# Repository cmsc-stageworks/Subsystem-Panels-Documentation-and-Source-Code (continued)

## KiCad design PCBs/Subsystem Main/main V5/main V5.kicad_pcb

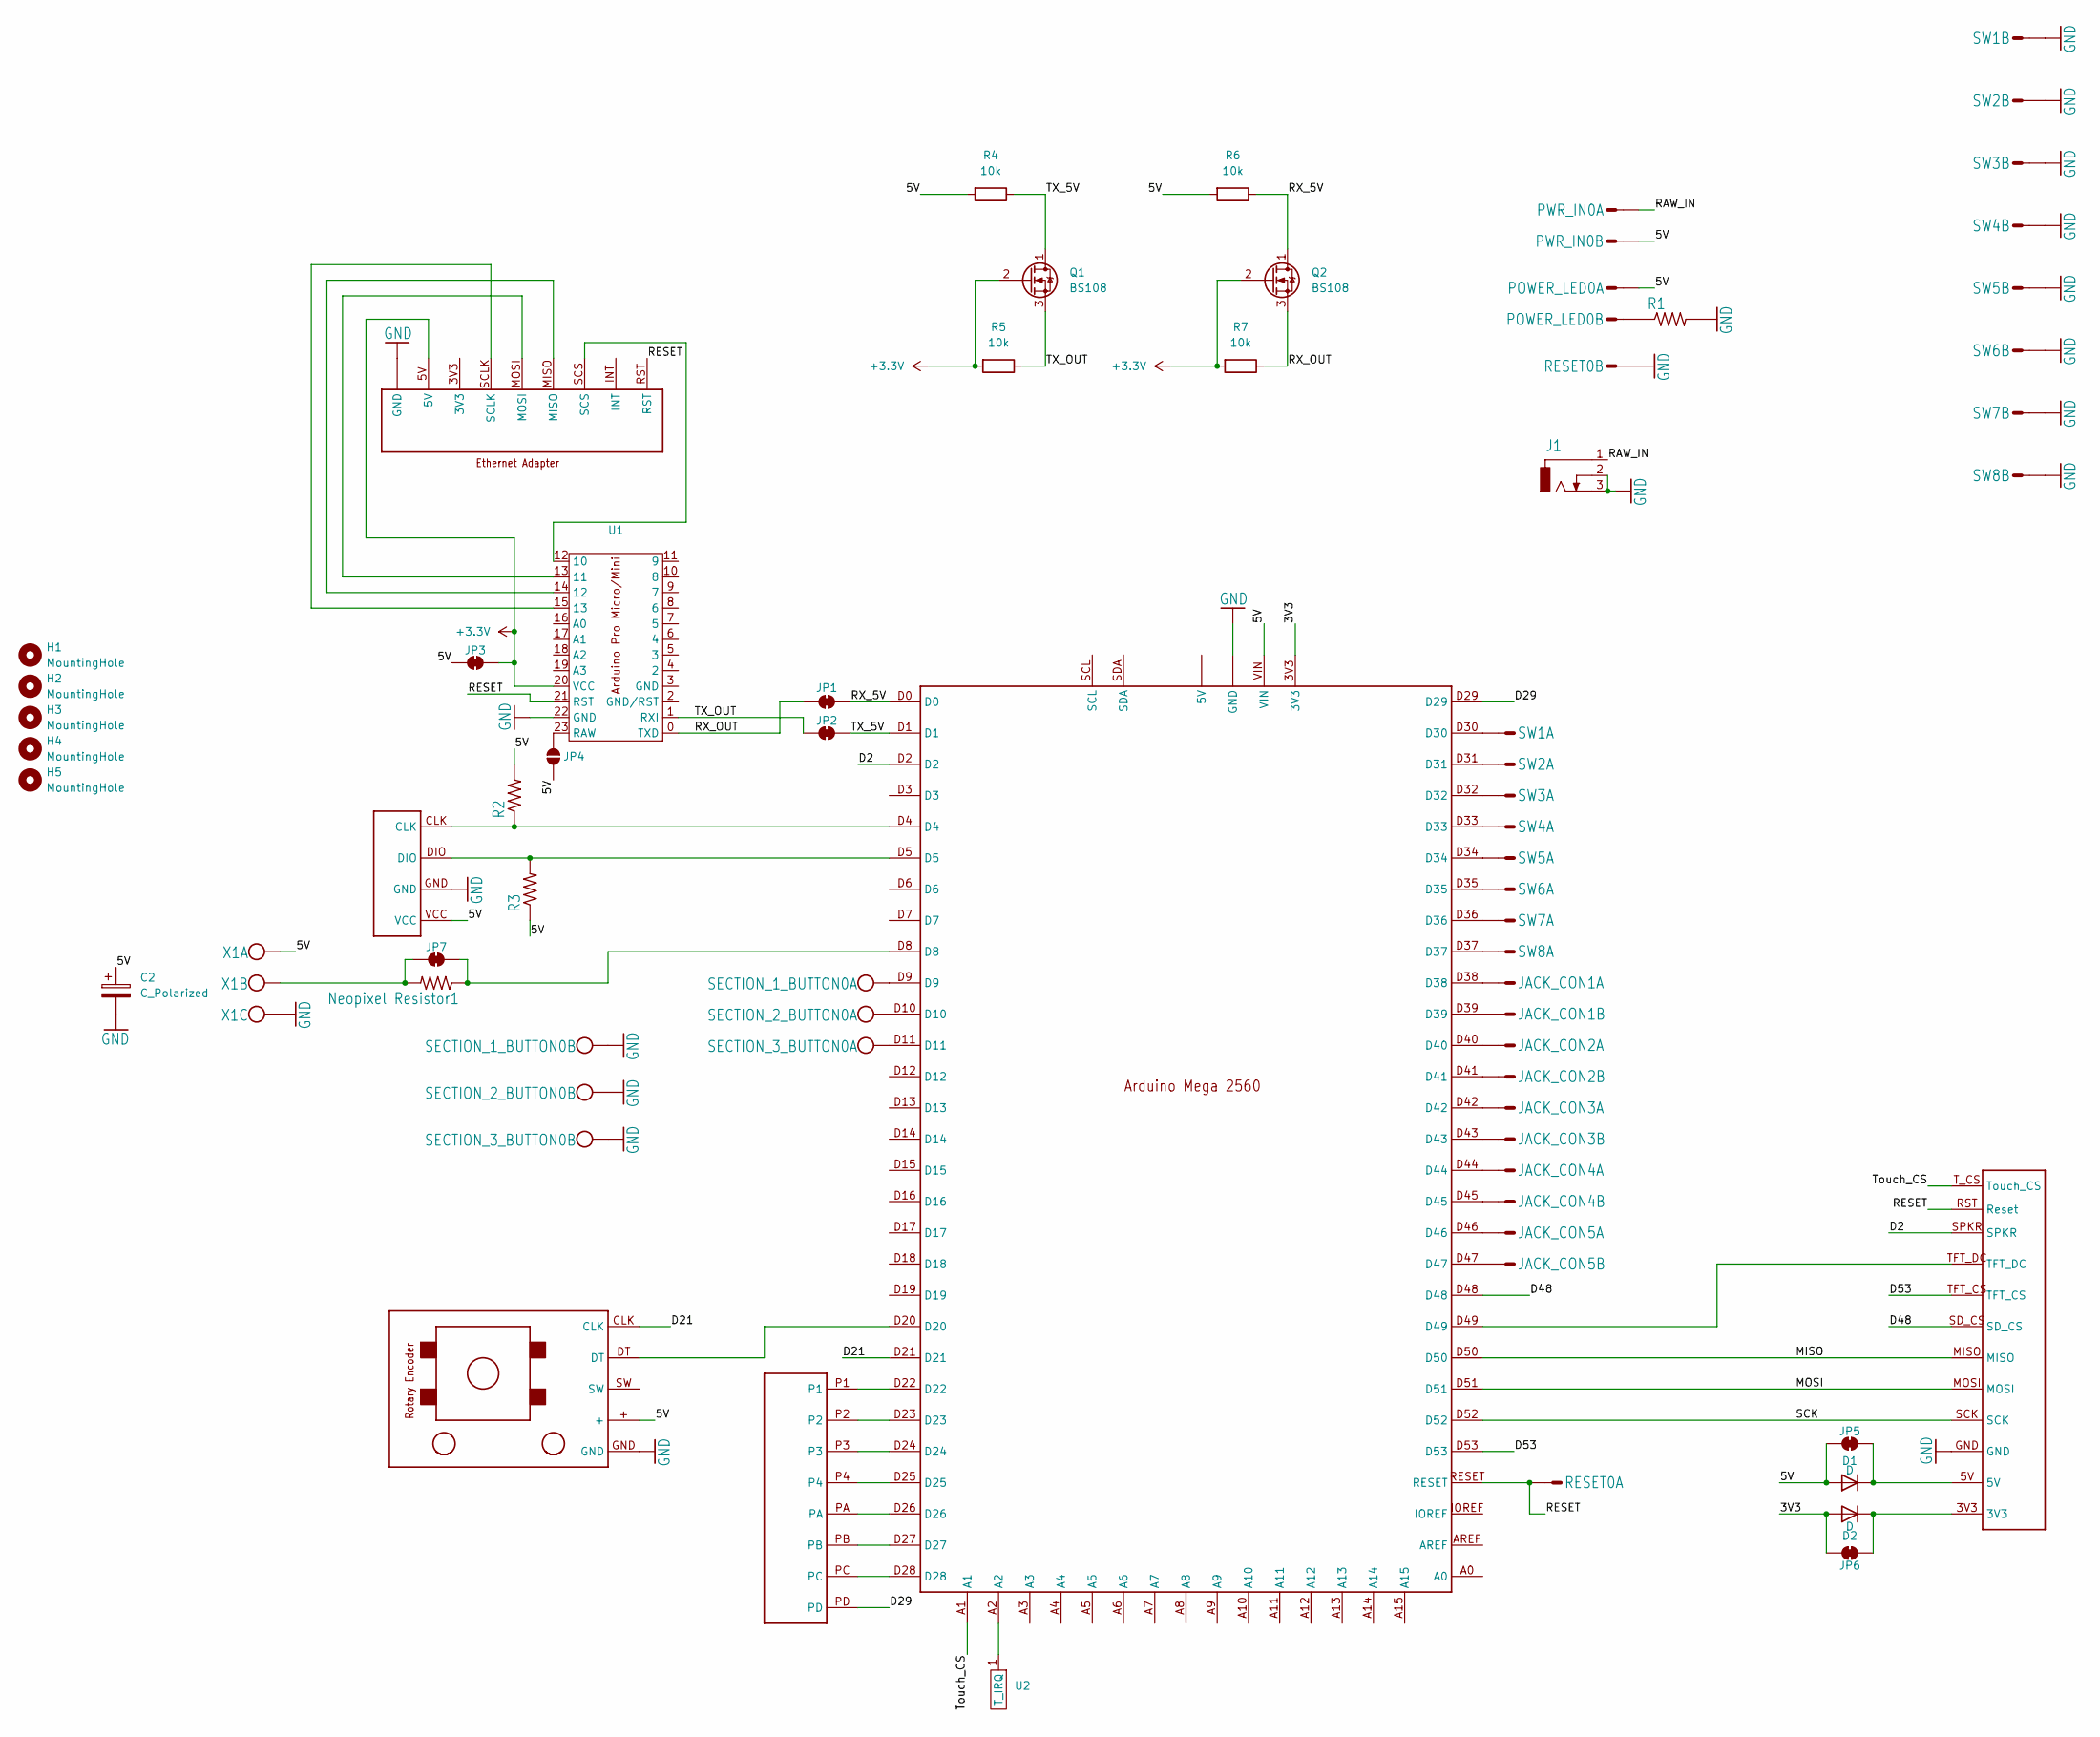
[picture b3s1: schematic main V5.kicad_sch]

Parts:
11: ETHERNET_ADAPTER
C1: SPI_HEADER_RIBBON_CONNECTOR_V2
C2: C_Polarized; CP_Radial_D10.0mm_P2.50mm_P5.00mm
D1, D2: D; D_DO-15_P10.16mm_Horizontal
H1, H2, H3, H4, H5: MountingHole; MountingHole_3.2mm_M3
J1: DCJ0303; BarrelJack_Horizontal
JACK_CON1, JACK_CON2, JACK_CON3, JACK_CON4, JACK_CON5: L02P; JST_EH_B2B-EH-A_1x02_P2.50mm_Vertical
JP1, JP2, JP3, JP5, JP6, JP7: SolderJumper_2_Bridged; SolderJumper-2_P1.3mm_Bridged_RoundedPad1.0x1.5mm
JP4: SolderJumper_2_Open; SolderJumper-2_P1.3mm_Open_TrianglePad1.0x1.5mm
Neopixel Resistor1: 350 ohm; R_Axial_DIN0204_L3.6mm_D1.6mm_P7.62mm_Horizontal
POWER_LED0: L02P; JST_EH_B2B-EH-A_1x02_P2.50mm_Vertical
PWR_IN0: L02P; JST_EH_B2B-EH-A_1x02_P2.50mm_Vertical
Q1, Q2: BS108; TO-92_Inline
R1: 220 ohm; R_Axial_DIN0204_L3.6mm_D1.6mm_P7.62mm_Horizontal
R2: 10K; R_Axial_DIN0204_L3.6mm_D1.6mm_P7.62mm_Horizontal
R3, R4, R5, R6, R7: 10k; R_Axial_DIN0204_L3.6mm_D1.6mm_P7.62mm_Horizontal
RESET0: L02P; JST_EH_B2B-EH-A_1x02_P2.50mm_Vertical
SECTION_1_BUTTON0, SECTION_2_BUTTON0, SECTION_3_BUTTON0: W237-102; JST_EH_B2B-EH-A_1x02_P2.50mm_Vertical
SW1, SW2, SW3, SW4, SW5, SW6, SW7, SW8: L02P; JST_EH_B2B-EH-A_1x02_P2.50mm_Vertical
U1: Arduino Pro Micro (Mini)
U2: T_IRQ
U$1: ARDUINO_MEGAMIRROR; ARDUINO_MEGA_MIRROR
U$2: 7_SEG_DISPLAY
U$4: BUTTON_GRID_HEADER; BUTTON_GRID_HEADER_RIBBON_CONNECTOR
U$5: ROTARY_ENCODER
X1: W237-103; TerminalBlock_bornier-3_P5.08mm

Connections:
+3.3V: 11.5V, JP3.2 (B), Q1.2 (G), Q2.2 (G), R5.2, R7.2, U1.20 (VCC)
/3V3: D2.2 (A), JP6.2 (B), U$1.3V3
/5V: C2.1, D1.2 (A), JP3.1 (A), JP4.1 (A), JP5.1 (A), POWER_LED0.1 (S), PWR_IN0.2 (S), R2.2, R3.1, R4.2, R6.2, U$1.VIN, U$2.VCC, U$5.+, X1.1 (KL)
/D2: C1.SPKR, U$1.D2
/D21: U$1.D21, U$5.CLK
/D29: U$1.D29, U$4.PD
/D48: C1.SD_CS, U$1.D48
/D53: C1.TFT_CS, U$1.D53
/MISO: C1.MISO, U$1.D50
/MOSI: C1.MOSI, U$1.D51
/RAW_IN: J1.1, PWR_IN0.1 (S)
/RESET: 11.RST, C1.RST (Reset), RESET0.1 (S), U1.21 (RST), U$1.RESET
/RX_5V: JP1.2 (B), Q2.1 (D), R6.1, U$1.D0
/RX_OUT: JP1.1 (A), Q2.3 (S), R7.1, U1.0 (TXD)
/SCK: C1.SCK, U$1.D52
/TX_5V: JP2.2 (B), Q1.1 (D), R4.1, U$1.D1
/TX_OUT: JP2.1 (A), Q1.3 (S), R5.1, U1.1 (RXI)
/Touch_CS: C1.T_CS (Touch_CS), U$1.A1
GND: 11.GND@1 (GND), 11.GND@2 (GND), C1.GND, C2.2, J1.2, J1.3, R1.2, RESET0.2 (S), SECTION_1_BUTTON0.2 (KL), SECTION_2_BUTTON0.2 (KL), SECTION_3_BUTTON0.2 (KL), SW1.2 (S), SW2.2 (S), SW3.2 (S), SW4.2 (S), SW5.2 (S), SW6.2 (S), SW7.2 (S), SW8.2 (S), U1.22 (GND), U$1.GND@1 (GND), U$1.GND@2 (GND), U$1.GND@3 (GND), U$1.GND@4 (GND), U$1.GND@5 (GND), U$2.GND, U$5.GND, X1.3 (KL)
unnamed: C1.TFT_DC, U$1.D49
unnamed: C1.5V, D1.1 (K), JP5.2 (B)
unnamed: C1.3V3, D2.1 (K), JP6.1 (A)
unnamed: JACK_CON1.1 (S), U$1.D38
unnamed: JACK_CON1.2 (S), U$1.D39
unnamed: JACK_CON2.1 (S), U$1.D40
unnamed: JACK_CON2.2 (S), U$1.D41
unnamed: JACK_CON3.1 (S), U$1.D42
unnamed: JACK_CON3.2 (S), U$1.D43
unnamed: JACK_CON4.1 (S), U$1.D44
unnamed: JACK_CON4.2 (S), U$1.D45
unnamed: JACK_CON5.1 (S), U$1.D46
unnamed: JACK_CON5.2 (S), U$1.D47
unnamed: JP4.2 (B), U1.23 (RAW)
unnamed: JP7.1 (A), Neopixel Resistor1.2, X1.2 (KL)
unnamed: JP7.2 (B), Neopixel Resistor1.1, U$1.D8
unnamed: POWER_LED0.2 (S), R1.1
unnamed: R2.1, U$1.D4, U$2.CLK
unnamed: R3.2, U$1.D5, U$2.DIO
unnamed: SECTION_1_BUTTON0.1 (KL), U$1.D9
unnamed: SECTION_2_BUTTON0.1 (KL), U$1.D10
unnamed: SECTION_3_BUTTON0.1 (KL), U$1.D11
unnamed: SW1.1 (S), U$1.D30
unnamed: SW2.1 (S), U$1.D31
unnamed: SW3.1 (S), U$1.D32
unnamed: SW4.1 (S), U$1.D33
unnamed: SW5.1 (S), U$1.D34
unnamed: SW6.1 (S), U$1.D35
unnamed: SW7.1 (S), U$1.D36
unnamed: SW8.1 (S), U$1.D37
unnamed: 11.SCS, U1.12 (10)
unnamed: 11.MOSI, U1.13 (11)
unnamed: 11.MISO, U1.14 (12)
unnamed: 11.SCLK, U1.15 (13)
unnamed: U2.1 (T_IRQ), U$1.A2
unnamed: U$1.5V@1 (5V), U$1.5V@2 (5V), U$1.5V@3 (5V)
unnamed: U$1.D20, U$5.DT
unnamed: U$1.D22, U$4.P1
unnamed: U$1.D23, U$4.P2
unnamed: U$1.D24, U$4.P3
unnamed: U$1.D25, U$4.P4
unnamed: U$1.D26, U$4.PA
unnamed: U$1.D27, U$4.PB
unnamed: U$1.D28, U$4.PC

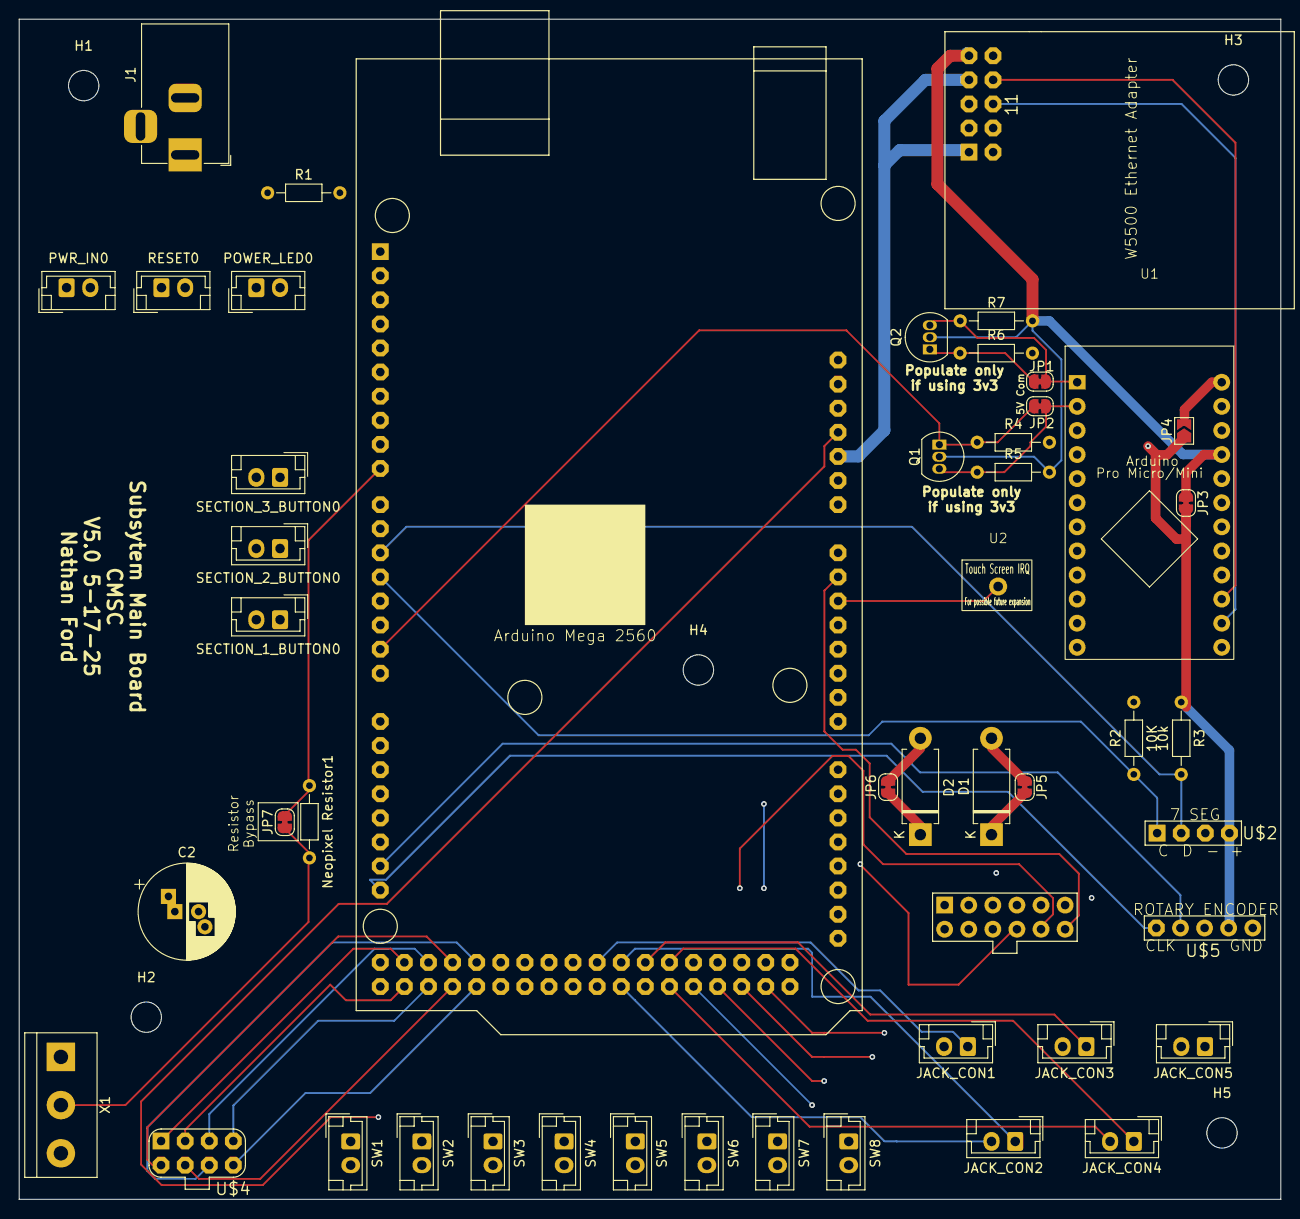
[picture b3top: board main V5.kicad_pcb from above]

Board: 4 copper layers, 133.0 x 124.4 mm, 54 parts (0 on the bottom side), 63 nets.

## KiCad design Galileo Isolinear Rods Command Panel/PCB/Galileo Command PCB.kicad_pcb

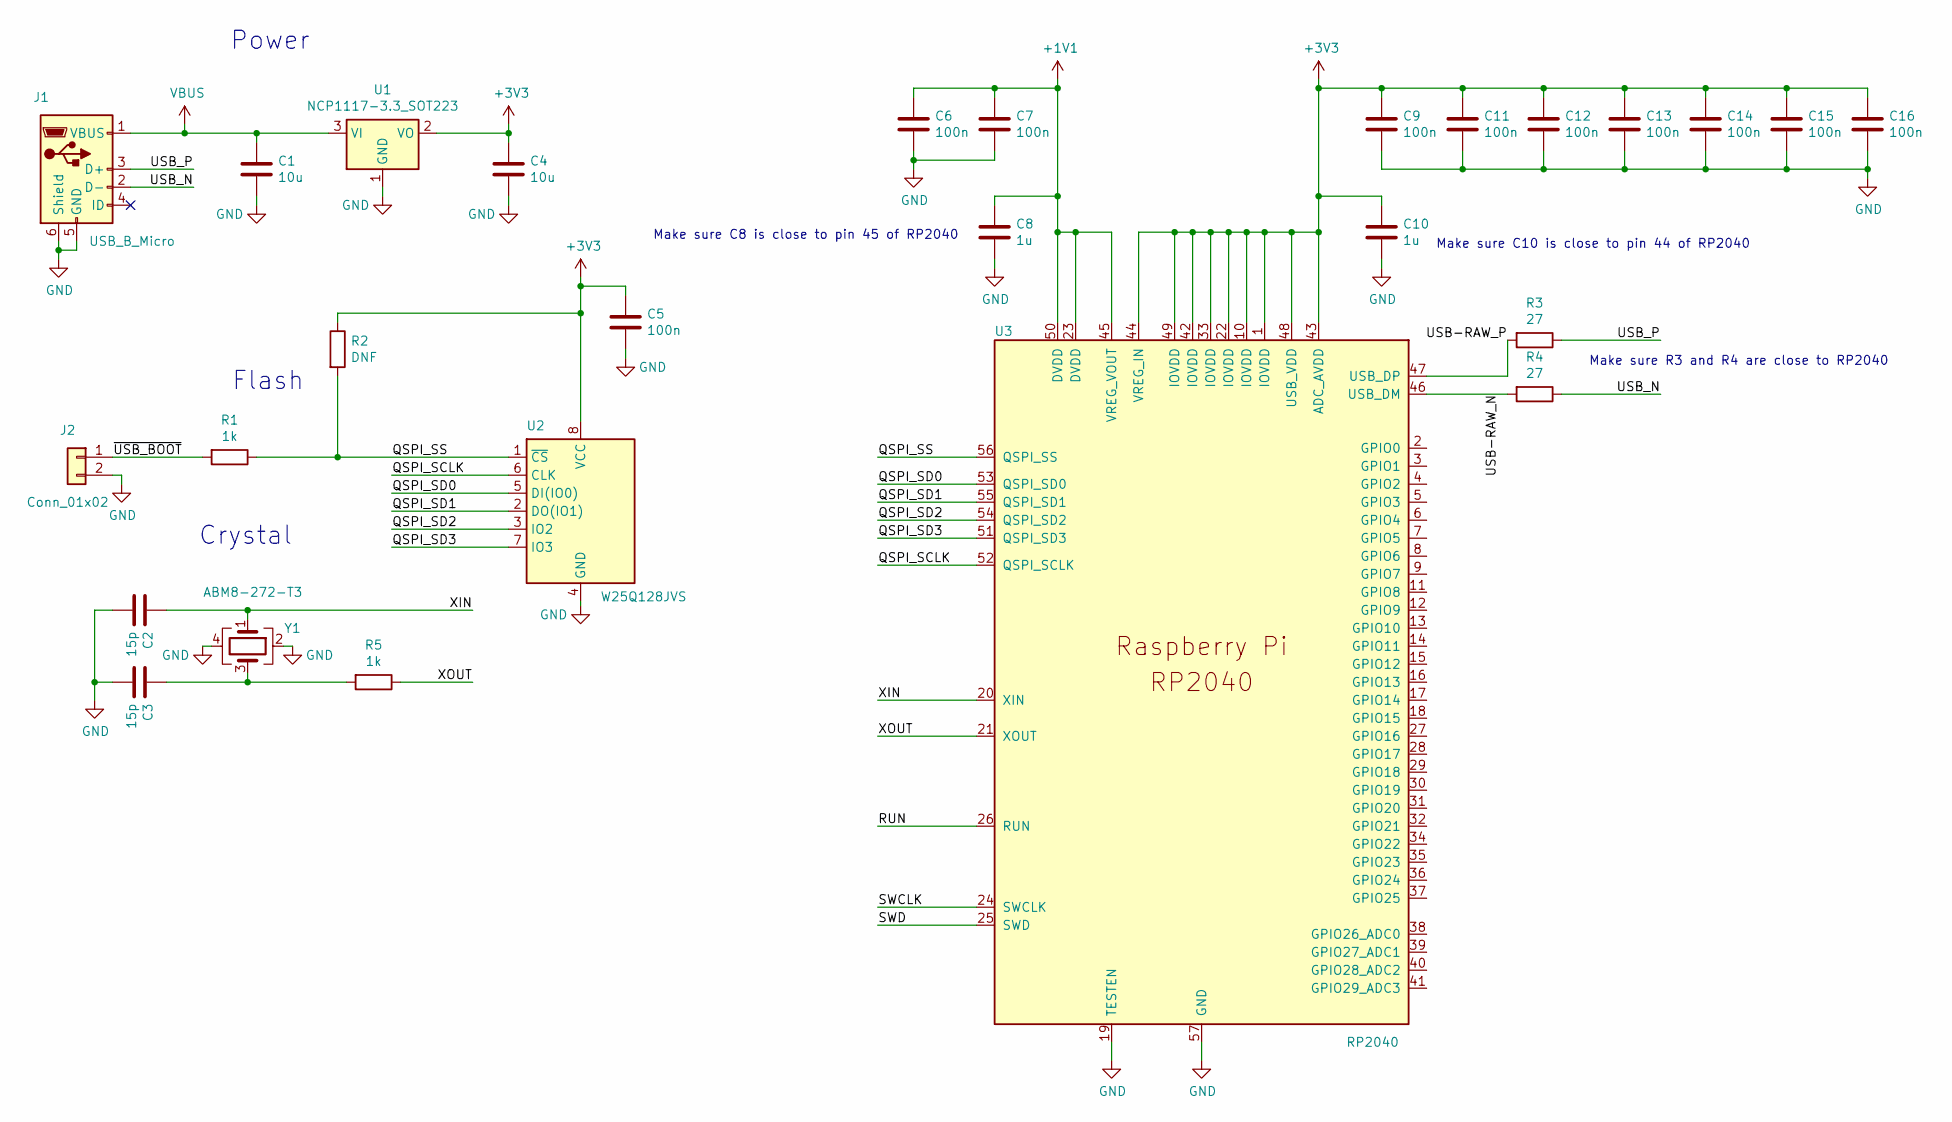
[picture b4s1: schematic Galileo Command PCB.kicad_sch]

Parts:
C1, C4: 10u; C_0805_2012Metric
C2, C3: 15p; C_0402_1005Metric
C5, C6, C7, C9, C11, C12, C13, C14, C15, C16: 100n; C_0402_1005Metric
C8, C10: 1u; C_0402_1005Metric
J1: USB_B_Micro; USB_Micro-B_Amphenol_10103594-0001LF_Horizontal_modified
J2: Conn_01x02; PinHeader_1x02_P2.54mm_Vertical
R1, R5: 1k; R_0402_1005Metric
R2: DNF; R_0402_1005Metric
R3, R4: 27; R_0402_1005Metric
U1: NCP1117-3.3_SOT223; SOT-223-3_TabPin2
U2: W25Q128JVS; SOIC-8_5.3x5.3mm_P1.27mm
U3: RP2040; RP2040-QFN-56
Y1: ABM8-272-T3; Crystal_SMD_3225-4Pin_3.2x2.5mm

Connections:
+1V1: C6.1, C7.1, C8.1, U3.23 (DVDD), U3.45 (VREG_VOUT), U3.50 (DVDD)
+3V3: C4.1, C5.1, C9.1, C10.1, C11.1, C12.1, C13.1, C14.1, C15.1, C16.1, R2.1, U1.2 (VO), U2.8 (VCC), U3.1 (IOVDD), U3.10 (IOVDD), U3.22 (IOVDD), U3.33 (IOVDD), U3.42 (IOVDD), U3.43 (ADC_AVDD), U3.44 (VREG_IN), U3.48 (USB_VDD), U3.49 (IOVDD)
/QSPI_SCLK: U2.6 (CLK), U3.52 (QSPI_SCLK)
/QSPI_SD0: U2.5 (DI(IO0)), U3.53 (QSPI_SD0)
/QSPI_SD1: U2.2 (DO(IO1)), U3.55 (QSPI_SD1)
/QSPI_SD2: U2.3 (IO2), U3.54 (QSPI_SD2)
/QSPI_SD3: U2.7 (IO3), U3.51 (QSPI_SD3)
/QSPI_SS: R1.1, R2.2, U2.1 (~CS), U3.56 (QSPI_SS)
/RUN: U3.26 (RUN)
/SWCLK: U3.24 (SWCLK)
/SWD: U3.25 (SWD)
/USB-RAW_N: R4.2, U3.46 (USB_DM)
/USB-RAW_P: R3.2, U3.47 (USB_DP)
/USB_N: J1.2 (D-), R4.1
/USB_P: J1.3 (D+), R3.1
/XIN: C2.1, U3.20 (XIN), Y1.1
/XOUT: R5.1, U3.21 (XOUT)
/~USB_BOOT: J2.1, R1.2
GND: C1.2, C2.2, C3.2, C4.2, C5.2, C6.2, C7.2, C8.2, C9.2, C10.2, C11.2, C12.2, C13.2, C14.2, C15.2, C16.2, J1.5 (GND), J1.6 (Shield), J2.2, U1.1 (GND), U2.4 (GND), U3.19 (TESTEN), U3.57 (GND), Y1.2, Y1.4
unnamed: C3.1, R5.2, Y1.3
VBUS: C1.1, J1.1 (VBUS), U1.3 (VI)

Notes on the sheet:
Make sure C10 is close to pin 44 of RP2040
Make sure R3 and R4 are close to RP2040
Power
Make sure C8 is close to pin 45 of RP2040
Flash
Crystal

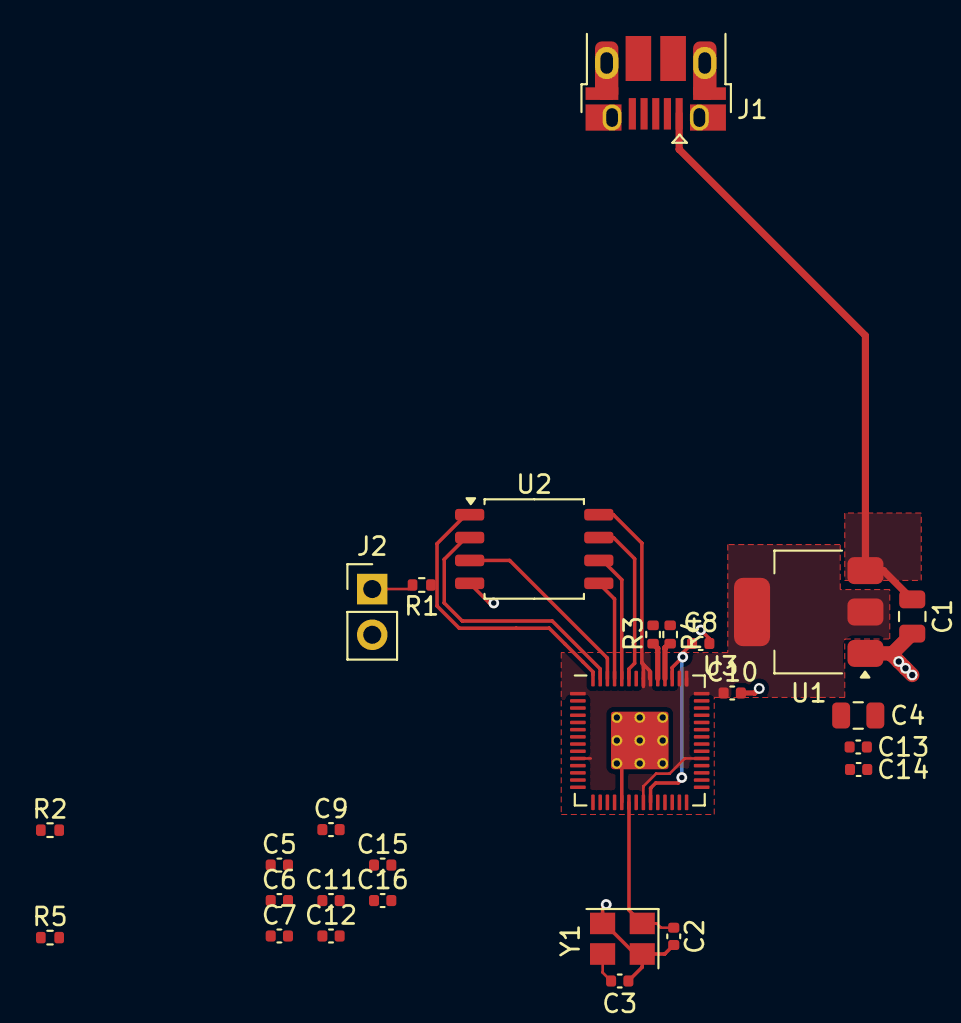
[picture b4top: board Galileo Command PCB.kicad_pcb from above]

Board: 2 copper layers, 27 parts (0 on the bottom side), 18 nets.

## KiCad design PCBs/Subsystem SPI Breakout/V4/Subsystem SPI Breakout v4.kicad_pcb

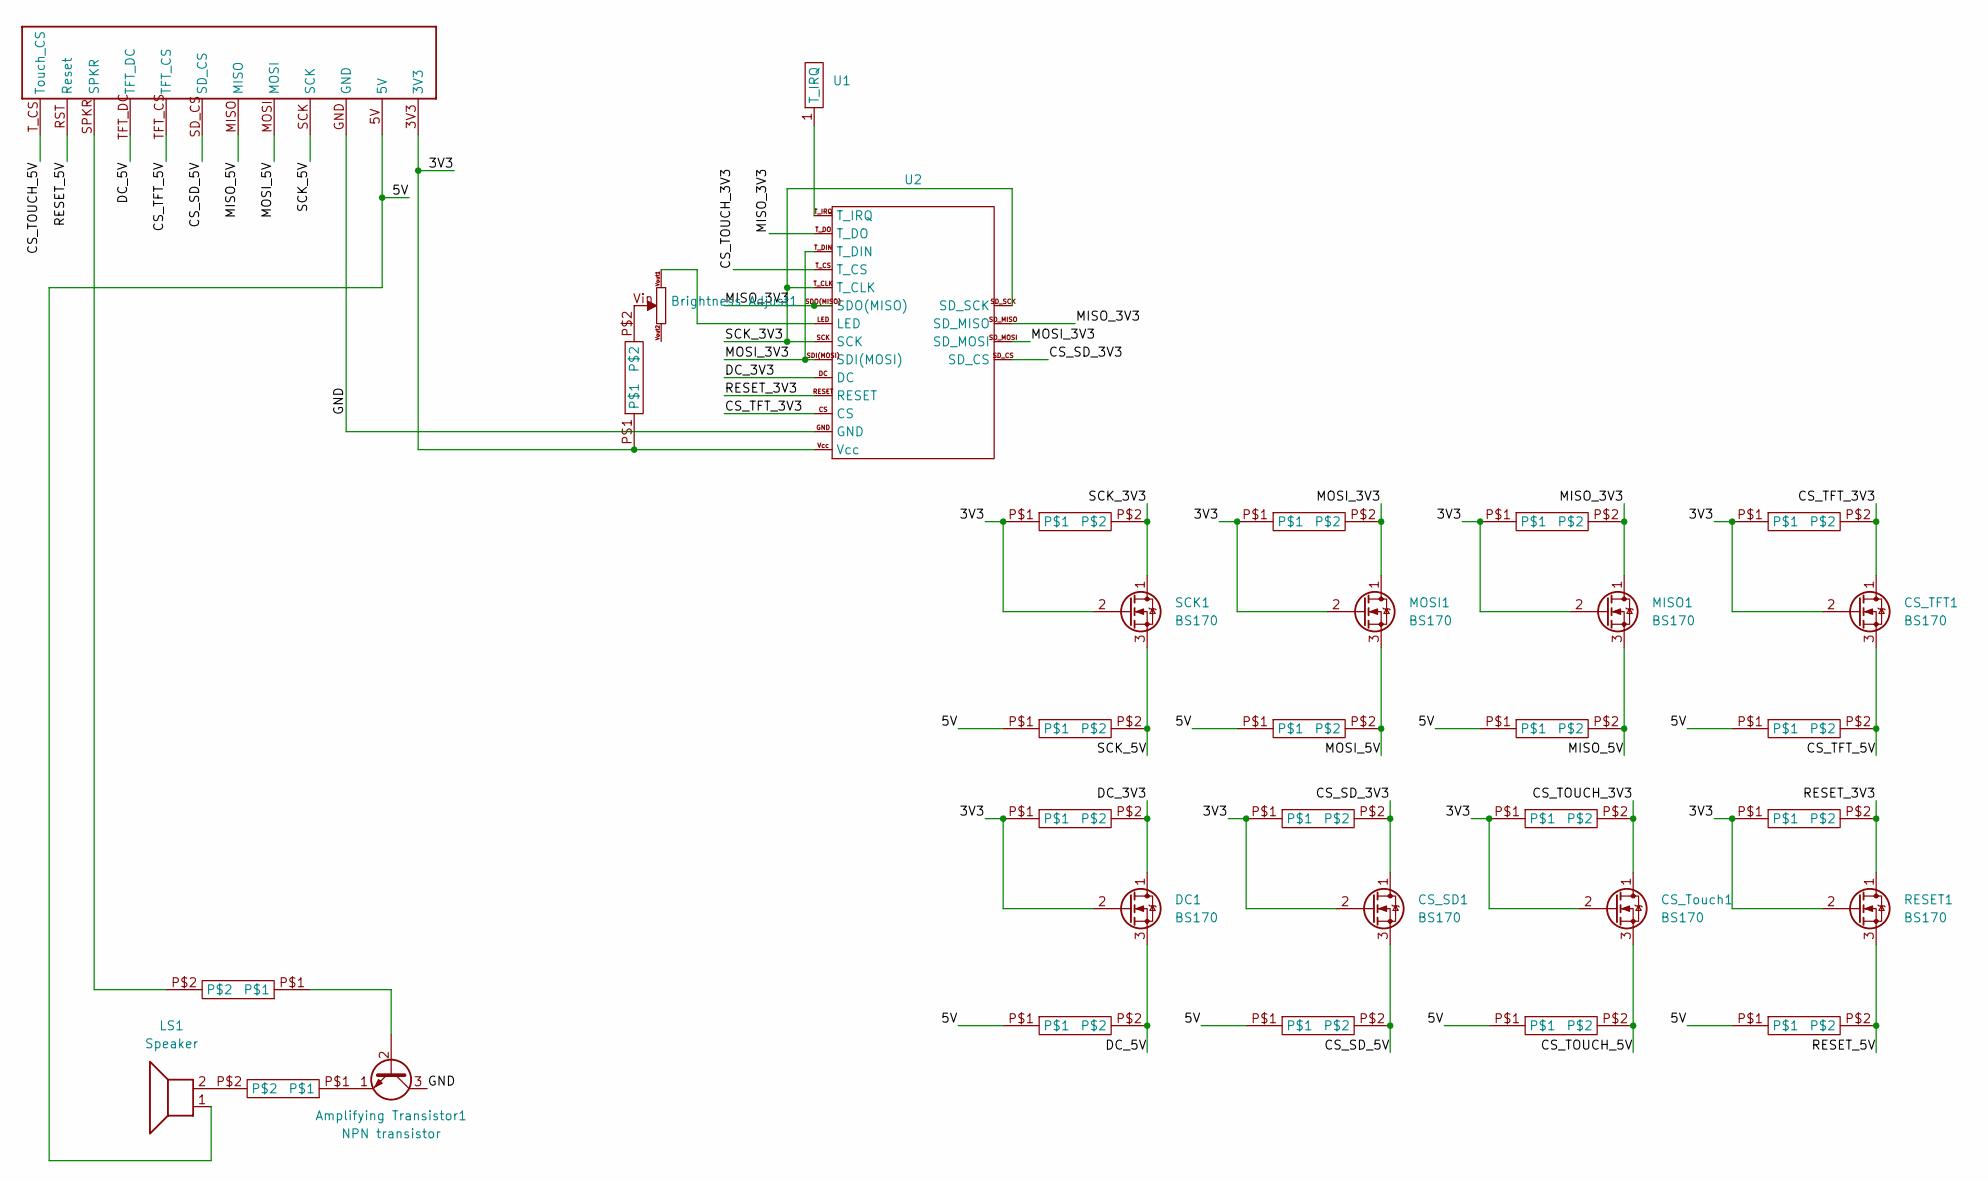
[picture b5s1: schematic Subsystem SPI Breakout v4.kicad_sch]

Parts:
Amplifying Transistor1: NPN transistor; TO-92_Inline
Brightness Adjust1: Small_Potentiometer
C1: SPI_HEADER_RIBBON_CONNECTOR_V2
CS_SD1: BS170; TO-92_Inline
CS_TFT1: BS170; TO-92_Inline
CS_Touch1: BS170; TO-92_Inline
DC1: BS170; TO-92_Inline
LS1: Speaker; TerminalBlock_bornier-2_P5.08mm
MISO1: BS170; TO-92_Inline
MOSI1: BS170; TO-92_Inline
R1, R2, R3, R4, R5, R6, R8, R10, R11, R12, R13, R14, R15, R16, R17, R18, R19: 10k Ω; THROUGH_HOLE_RESISTOR
R7: 10 Ω; THROUGH_HOLE_RESISTOR
R9: 100 Ω; THROUGH_HOLE_RESISTOR
RESET1: BS170; TO-92_Inline
SCK1: BS170; TO-92_Inline
U1: T_IRQ
U2: 2.8__TFT_SPI_ILI9341_WITH_SD_CARD

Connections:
/3V3: C1.3V3, CS_SD1.2 (G), CS_TFT1.2 (G), CS_Touch1.2 (G), DC1.2 (G), MISO1.2 (G), MOSI1.2 (G), R1.P$1, R3.P$1, R5.P$1, R9.P$1, R10.P$1, R12.P$1, R14.P$1, R16.P$1, R18.P$1, RESET1.2 (G), SCK1.2 (G), U2.Vcc
/5V: C1.5V, LS1.1, R2.P$1, R4.P$1, R6.P$1, R11.P$1, R13.P$1, R15.P$1, R17.P$1, R19.P$1
/CS_SD_3V3: CS_SD1.1 (D), R14.P$2, U2.SD_CS
/CS_SD_5V: C1.SD_CS, CS_SD1.3 (S), R15.P$2
/CS_TFT_3V3: CS_TFT1.1 (D), R10.P$2, U2.CS
/CS_TFT_5V: C1.TFT_CS, CS_TFT1.3 (S), R11.P$2
/CS_TOUCH_3V3: CS_Touch1.1 (D), R16.P$2, U2.T_CS
/CS_TOUCH_5V: C1.T_CS (Touch_CS), CS_Touch1.3 (S), R17.P$2
/DC_3V3: DC1.1 (D), R12.P$2, U2.DC
/DC_5V: C1.TFT_DC, DC1.3 (S), R13.P$2
/GND: Amplifying Transistor1.3 (C), C1.GND, U2.GND
/MISO_3V3: MISO1.1 (D), R5.P$2, U2.SDO(MISO), U2.SD_MISO, U2.T_DO
/MISO_5V: C1.MISO, MISO1.3 (S), R6.P$2
/MOSI_3V3: MOSI1.1 (D), R3.P$2, U2.SDI(MOSI), U2.SD_MOSI, U2.T_DIN
/MOSI_5V: C1.MOSI, MOSI1.3 (S), R4.P$2
/RESET_3V3: R18.P$2, RESET1.1 (D), U2.RESET
/RESET_5V: C1.RST (Reset), R19.P$2, RESET1.3 (S)
/SCK_3V3: R1.P$2, SCK1.1 (D), U2.SCK, U2.SD_SCK, U2.T_CLK
/SCK_5V: C1.SCK, R2.P$2, SCK1.3 (S)
unnamed: Amplifying Transistor1.2 (B), R8.P$1
unnamed: Amplifying Transistor1.1 (E), R7.P$1
unnamed: Brightness Adjust1.Vin, R9.P$2
unnamed: Brightness Adjust1.Vout1, U2.LED
unnamed: C1.SPKR, R8.P$2
unnamed: LS1.2, R7.P$2
unnamed: U1.1 (T_IRQ), U2.T_IRQ

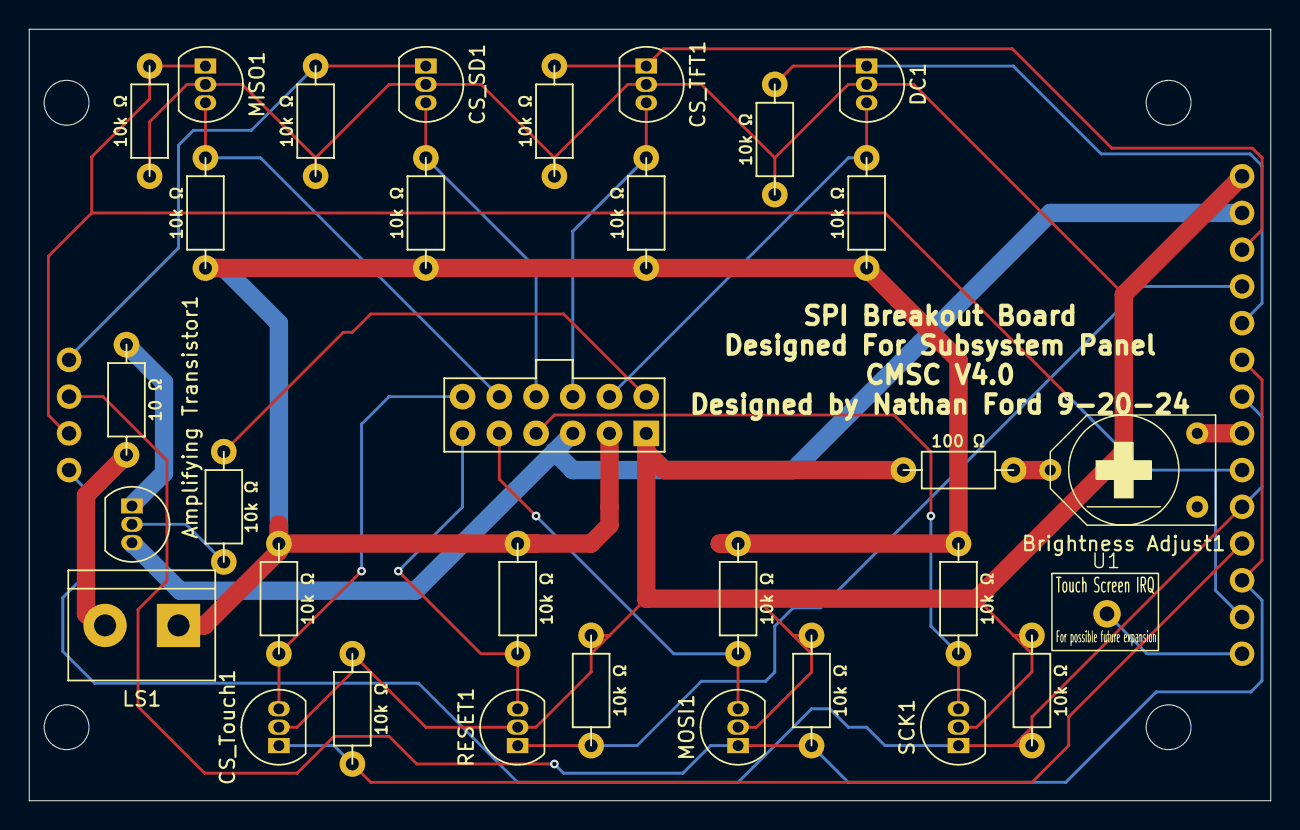
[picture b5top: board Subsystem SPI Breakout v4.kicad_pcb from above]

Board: 2 copper layers, 85.8 x 53.3 mm, 33 parts (0 on the bottom side), 26 nets.

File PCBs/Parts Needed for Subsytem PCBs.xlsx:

Subsystem PCB parts list
Main Board
Part | Quantity (Per board) | notes | link | alt link
220 Ω Resistor | 1 | To drive the power LED, I think we have many on hand
390 Ω Resistor | 1 | Optional, to stabilize NeoPixels | Ali-Express
10k Ω Resistor | 2 |  | Ali-Express
Diodes | 2 |  | Ali-Express
DC Barrel Jack | 1 |  | Ali-Express
Capacitor | 1 | 1000uF (Optional, to stabilize NeoPixels) | Ali-Express
JST/Pin headers | 19 (2x pin headers) | I have listed the JST headers as the second option, because I have had problems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 | Pin Headers | JST Headers
Ethernet SPI | 1 | We have them on hand already I believe? | Ali-Express
Male Pin Header | 85 (pin count) | For the mega, it is prefered that we have at least 3 40 pin headers for each me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 | Ali-Express
Arduino mega 2650 | 1 | The ones we already have should work fine. Not the compact form factor. USB C o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 | Ali Express
Header Pins | 1x (1x4) 1x (1x5) | Rotary Encoder/7 Seg Display | Ali-Express
Arduino Pro Mini | 1 | 5V model. The following has the correct pinout | Ali-Express
Programmer for Pro Mini | 1 in total for all 5 | Just needed to update software, FT232RL, This one will allow us to hold it in p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 | Ali-Express
Pin Header (2x4) | 1 | For button board breakout | Ali-Express
Pin Header (2x6) | 1 | For SPI Board | Ali-Express
Ribbon Cables | 1x (2x4) 1x (2x6) | For button board and SPI board, with enough length to reach, I don't remember t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 | Ali-Express | If we want to make custom length ones
Screw Block Terminal | 1x (1x3) | For neopixels | Ali-Express
SPI Board
Part | Quantity (Per board) | notes | link | alt link
Pin Header (2x6) | 1 | For SPI Board | Ali-Express
10k Ω Resistor | 15 |  | Ali-Express
10 Ω Resistor | 1 | For speaker must be >3W, 5W is safer | Ali-Express
100 Ω Resistor | 1 | For screen, doesn't need to be high power | Ali-Express
2N2222 Transistor | 1 | We have this on hand, or at least I was told
BS170 MOSFET | 7 |  | Ali-Express
Screen Dim Potentiometer | 1 | I would go somewhere between 200-500, because we don't want it too dim, but if 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 | Ali-Express
Screw Block Terminal | 1 | For the Speaker
ILI9137 screen | 1 | We already have them | Ali-Express
Button Board
Part | Quantity (Per board) | notes | link | alt link
Pin Header (2x4) | 1 | For button board breakout | Ali-Express
JST/Pin headers | 16 (2x pin headers) | I have listed the JST headers as the second option, because I have had problems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 | Pin Headers | JST Headers

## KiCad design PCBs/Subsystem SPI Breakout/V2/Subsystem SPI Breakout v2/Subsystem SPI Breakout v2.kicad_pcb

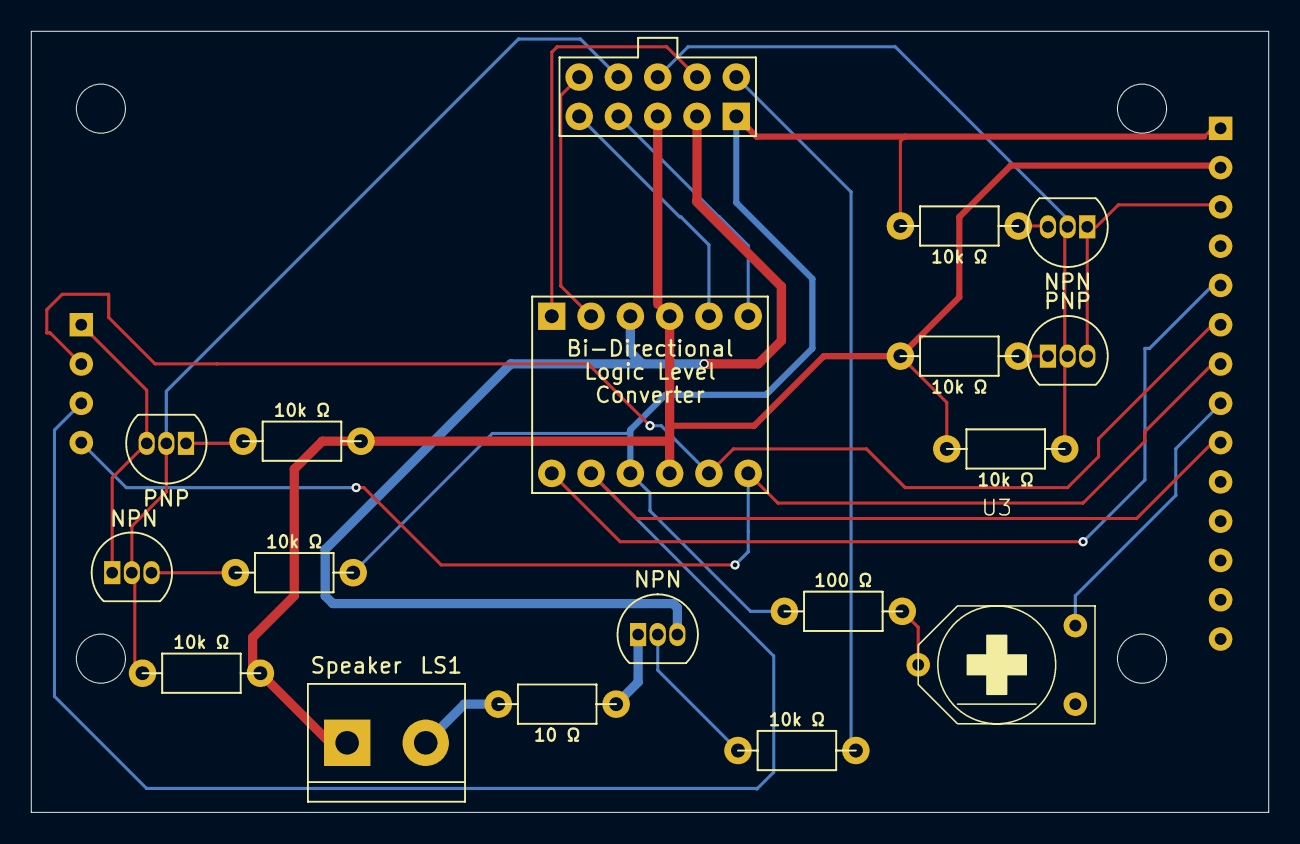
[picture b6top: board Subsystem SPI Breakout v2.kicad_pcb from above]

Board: 2 copper layers, 80.0 x 50.5 mm, 19 parts (0 on the bottom side), 25 nets.

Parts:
1: SPI_HEADER_RIBBON_CONNECTOR
LS1: Speaker; TerminalBlock_bornier-2_P5.08mm
LogicConverter1: BI_DIRECTIONAL_LOGIC_LEVEL_CONVERTER
NPN: NPN transistor; TO-92_Inline
NPN#2, NPN#3: NPN transistor; TO-92_Inline
PNP: PNP Transistor; TO-92_Inline
PNP#2: PNP Transistor; TO-92_Inline
R1, R2, R3, R4, R5, R6, R8: 10k Ω; THROUGH_HOLE_RESISTOR
R7: 10 Ω; THROUGH_HOLE_RESISTOR
R9: 100 Ω; THROUGH_HOLE_RESISTOR
U2: 2.4'_TFT_SPI_ILI9341_WITH_SD_CARD
U3: Small_Potentiometer

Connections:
unnamed: 1.3V3, LogicConverter1.LV, R1.P$2, R2.P$2, R9.P$1, U2.Vcc
unnamed: 1.GND, LS1.1, LogicConverter1.GND1, LogicConverter1.GND2, R3.P$2, R4.P$2, R5.P$2, R6.P$2, U2.GND
unnamed: 1.MISO, LogicConverter1.HV2
unnamed: 1.MOSI, LogicConverter1.HV3
unnamed: 1.SCK, LogicConverter1.HV4
unnamed: 1.SPKR, R8.P$2
unnamed: 1.TFT_DC, LogicConverter1.HV1
unnamed: LS1.2, R7.P$2
unnamed: LogicConverter1.LV1, U2.DC
unnamed: LogicConverter1.LV2, U2.SDO(MISO), U2.SD_MISO
unnamed: LogicConverter1.LV3, U2.SDI(MOSI), U2.SD_MOSI
unnamed: LogicConverter1.LV4, U2.SCK, U2.SD_SCK
unnamed: 1.TFT_CS, NPN#2.2 (B), PNP.2 (B), R6.P$1
unnamed: NPN#2.1 (E), PNP.3 (C), U2.CS
unnamed: PNP.1 (E), R4.P$1
unnamed: NPN#2.3 (C), R1.P$1
unnamed: 1.SD_CS, NPN#3.2 (B), PNP#2.2 (B), R5.P$1
unnamed: NPN#3.1 (E), PNP#2.3 (C), U2.SD_CS
unnamed: PNP#2.1 (E), R3.P$1
unnamed: NPN#3.3 (C), R2.P$1
unnamed: NPN.2 (B), R8.P$1
unnamed: 1.5V, LogicConverter1.HV, NPN.3 (C)
unnamed: NPN.1 (E), R7.P$1
unnamed: R9.P$2, U3.Vin
unnamed: U2.LED, U3.Vout1

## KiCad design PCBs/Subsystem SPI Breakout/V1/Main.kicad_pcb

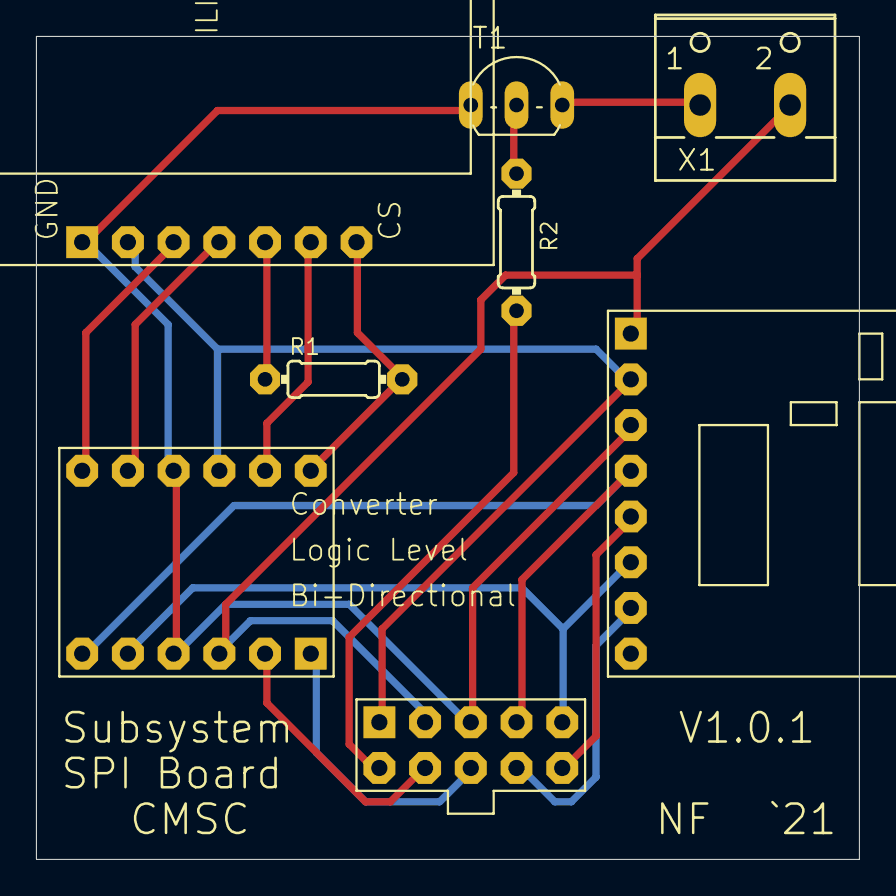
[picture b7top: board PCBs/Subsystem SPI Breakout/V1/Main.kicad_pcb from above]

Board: 2 copper layers, 45.7 x 45.7 mm, 8 parts (0 on the bottom side), 17 nets.

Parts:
R1: 100kΩ; 0204_7_420
R2: 1kΩ; 0204_7_420
T1: 2N2222; TO92-EBC-OVAL_420
U$1: ILI9341; ILI9341_FOOTPRINT
U$2: BI_DIRECTIONAL_LOGIC_LEVEL_CONVERTER
U$3: SD_CARD_READER
U$4: HEADERRIBBON_CONNECTOR; HEADER_RIBBON_CONNECTOR
X1: W237-102_195

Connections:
+3V3: U$1.VCC, U$2.LV, U$3.3V, U$4.3V3
+5V: U$2.HV, U$3.5V, U$4.5V, X1.2
DC: U$2.HV2, U$4.TFT_DC
GND: T1.E, U$1.GND, U$2.GND1, U$2.GND2, U$3.GND, U$4.GND
unnamed: T1.C, X1.1
unnamed: U$1.SCK, U$2.LV4
unnamed: U$1.SDA, U$2.LV3
unnamed: U$1.DC, U$2.LV2
unnamed: R1.2, U$1.CS, U$2.LV1
unnamed: R2.1, T1.B
SCK: U$2.HV4, U$3.CLK, U$4.SCK
SDI: U$2.HV3, U$3.DI, U$4.MOSI
SDO: U$3.DO, U$4.MISO
SD_CS: U$3.CS, U$4.SD_CS
SPKR: R2.2, U$4.SPKR
TFT_CS: U$2.HV1, U$4.TFT_CS
TFT_RST: R1.1, U$1.RST

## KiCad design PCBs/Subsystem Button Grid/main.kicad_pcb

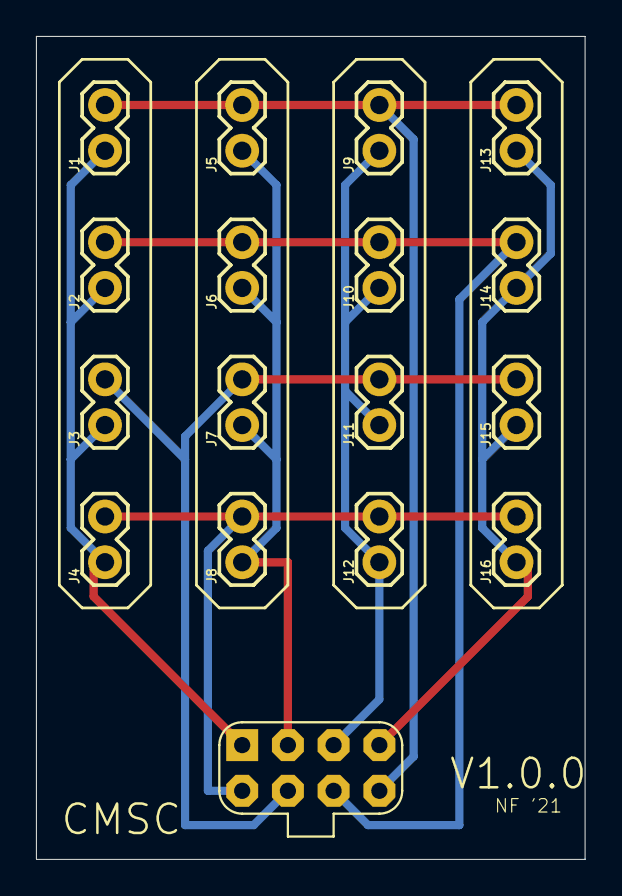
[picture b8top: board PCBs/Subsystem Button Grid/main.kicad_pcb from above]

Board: 2 copper layers, 30.5 x 45.7 mm, 17 parts (0 on the bottom side), 8 nets.

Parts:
J1, J2, J3, J4, J5, J6, J7, J8, J9, J10, J11, J12, J13, J14, J15, J16: 1X02
U$1: BUTTON_GRID_HEADER; BUTTON_GRID_HEADER_RIBBON_CONNECTOR

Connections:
unnamed: J1.1, J2.1, J3.1, J4.1, U$1.P1
unnamed: J5.1, J6.1, J7.1, J8.1, U$1.P2
unnamed: J9.1, J10.1, J11.1, J12.1, U$1.P3
unnamed: J13.1, J14.1, J15.1, J16.1, U$1.P4
PA: J4.2, J8.2, J12.2, J16.2, U$1.PA
PB: J3.2, J7.2, J11.2, J15.2, U$1.PB
PC: J2.2, J6.2, J10.2, J14.2, U$1.PC
PD: J1.2, J5.2, J9.2, J13.2, U$1.PD
